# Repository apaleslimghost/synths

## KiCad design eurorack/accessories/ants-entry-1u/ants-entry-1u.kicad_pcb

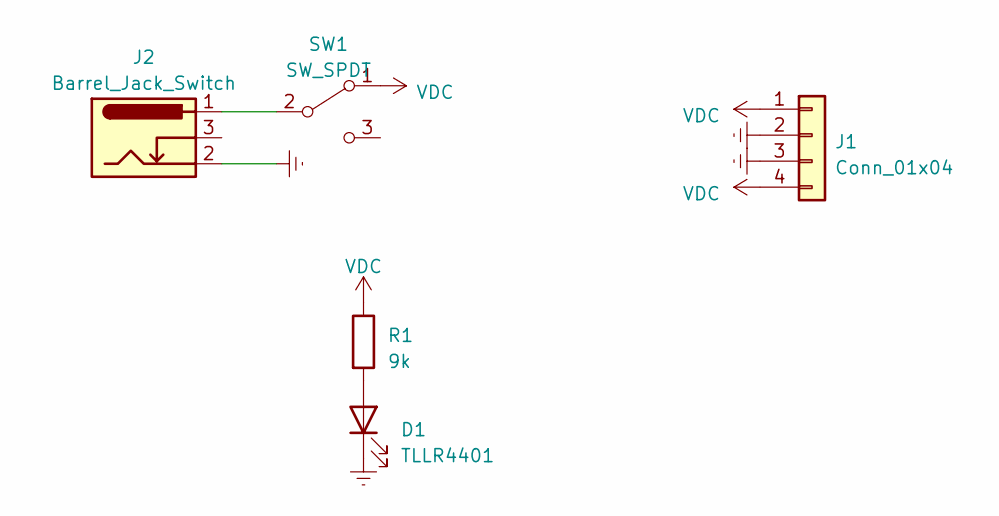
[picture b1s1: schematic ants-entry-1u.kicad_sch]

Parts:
D1: TLLR4401; LED_D3.0mm
J1: Conn_01x04; Molex_KK-254_AE-6410-04A_1x04_P2.54mm_Horizontal
J2: Barrel_Jack_Switch; CUI_PJ-064B
R1: 9k; R_Axial_DIN0207_L6.3mm_D2.5mm_P7.62mm_Horizontal
SW1: SW_SPDT; Sub Mini Toggle Switch SPDT

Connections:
Earth: D1.1 (K), J1.2, J1.3, J2.2
unnamed: D1.2 (A), R1.2
unnamed: J2.1, SW1.2 (B)
VDC: J1.1, J1.4, R1.1, SW1.1 (A)

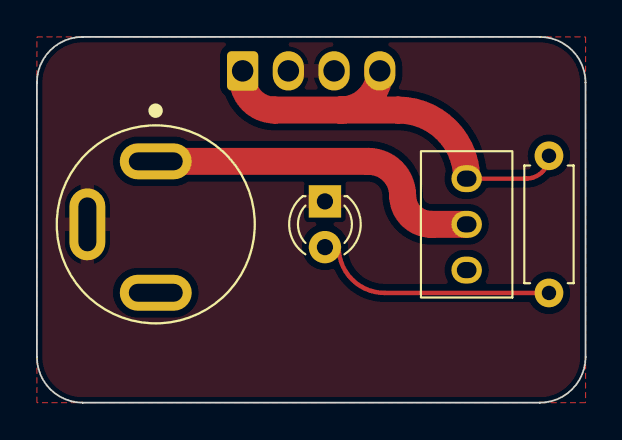
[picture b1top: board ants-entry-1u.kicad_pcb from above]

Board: 2 copper layers, 30.5 x 20.3 mm, 5 parts (1 on the bottom side), 4 nets.

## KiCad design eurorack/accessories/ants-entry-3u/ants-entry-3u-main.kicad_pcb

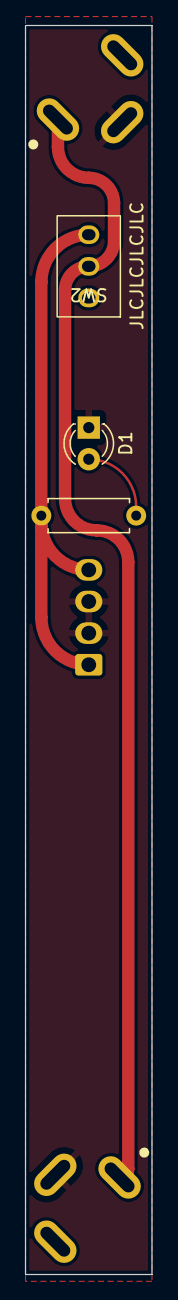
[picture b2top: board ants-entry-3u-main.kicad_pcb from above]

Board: 2 copper layers, 10.2 x 100.3 mm, 6 parts (1 on the bottom side), 4 nets.

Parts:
D1: TLLR4401; LED_D3.0mm
J1: Conn_01x04; Molex_KK-254_AE-6410-04A_1x04_P2.54mm_Vertical
J2, J3: Barrel_Jack_Switch; CUI_PJ-064B
R1: 9k; R_Axial_DIN0207_L6.3mm_D2.5mm_P7.62mm_Horizontal
SW2: SW_SPDT; Sub Mini Toggle Switch SPDT

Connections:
Earth: D1.1 (K), J1.2, J1.3, J2.2, J3.2
unnamed: D1.2 (A), R1.2
unnamed: J2.1, J3.1, SW2.2 (B)
VDC: J1.1, J1.4, R1.1, SW2.1 (A)

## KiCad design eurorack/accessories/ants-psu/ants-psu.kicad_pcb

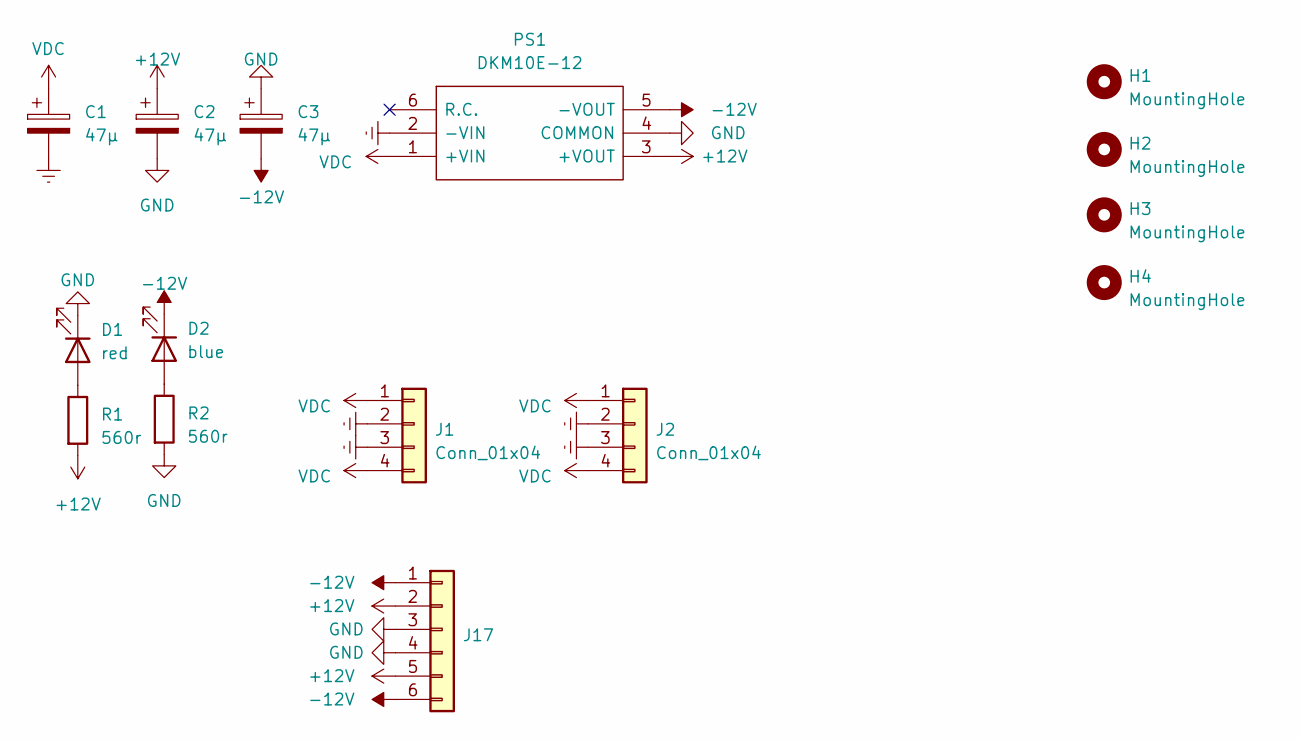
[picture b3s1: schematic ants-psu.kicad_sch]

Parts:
C1, C2, C3: 47μ; CP_Elec_5x4.5
D1: red; LED_0805_2012Metric_Pad1.15x1.40mm_HandSolder
D2: blue; LED_0805_2012Metric_Pad1.15x1.40mm_HandSolder
H1, H2, H3, H4: MountingHole; MountingHole_3.2mm_M3
J1, J2: Conn_01x04; Molex_KK-254_AE-6410-04A_1x04_P2.54mm_Horizontal
J17: Conn_01x06; Molex_KK-254_AE-6410-06A_1x06_P2.54mm_Horizontal
PS1: DKM10E-12; DKM10E12; Manufacturer_Part_Number DKM10E-12; Mouser Part Number 709-DKM10E-12
R1, R2: 560r; R_0805_2012Metric_Pad1.20x1.40mm_HandSolder

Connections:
+12V: C2.1, PS1.3 (+VOUT), R1.2; also elsewhere on the board
-12V: C3.2, D2.1 (K), PS1.5 (-VOUT); also elsewhere on the board
Earth: C1.2, J1.2, J1.3, J2.2, J2.3, PS1.2 (-VIN)
GND: C2.2, C3.1, D1.1 (K), PS1.4 (COMMON), R2.2; also elsewhere on the board
unnamed: D1.2 (A), R1.1
unnamed: D2.2 (A), R2.1
VDC: C1.1, J1.1, J1.4, J2.1, J2.4, PS1.1 (+VIN)

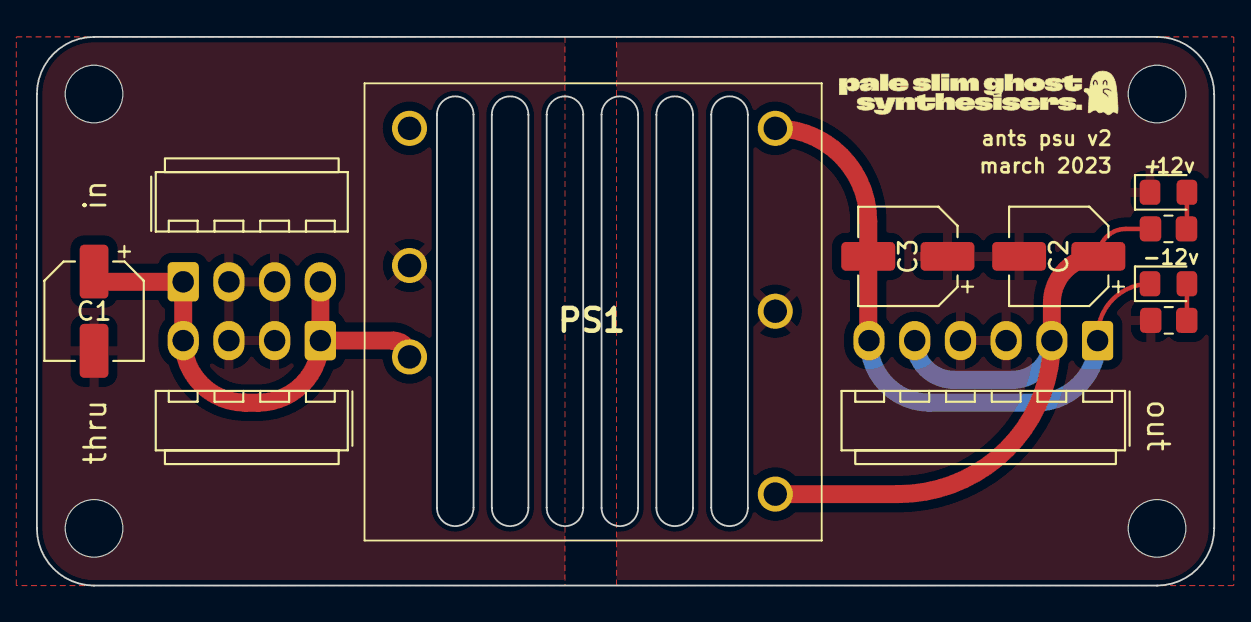
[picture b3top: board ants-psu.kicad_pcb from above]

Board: 2 copper layers, 65.4 x 30.5 mm, 15 parts (0 on the bottom side), 7 nets.

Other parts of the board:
J3: Conn_01x06; Molex_KK-254_AE-6410-06A_1x06_P2.54mm_Horizontal

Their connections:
+12V: J3.2, J3.5; also elsewhere on the board
-12V: J3.1, J3.6; also elsewhere on the board
GND: J3.3, J3.4; also elsewhere on the board

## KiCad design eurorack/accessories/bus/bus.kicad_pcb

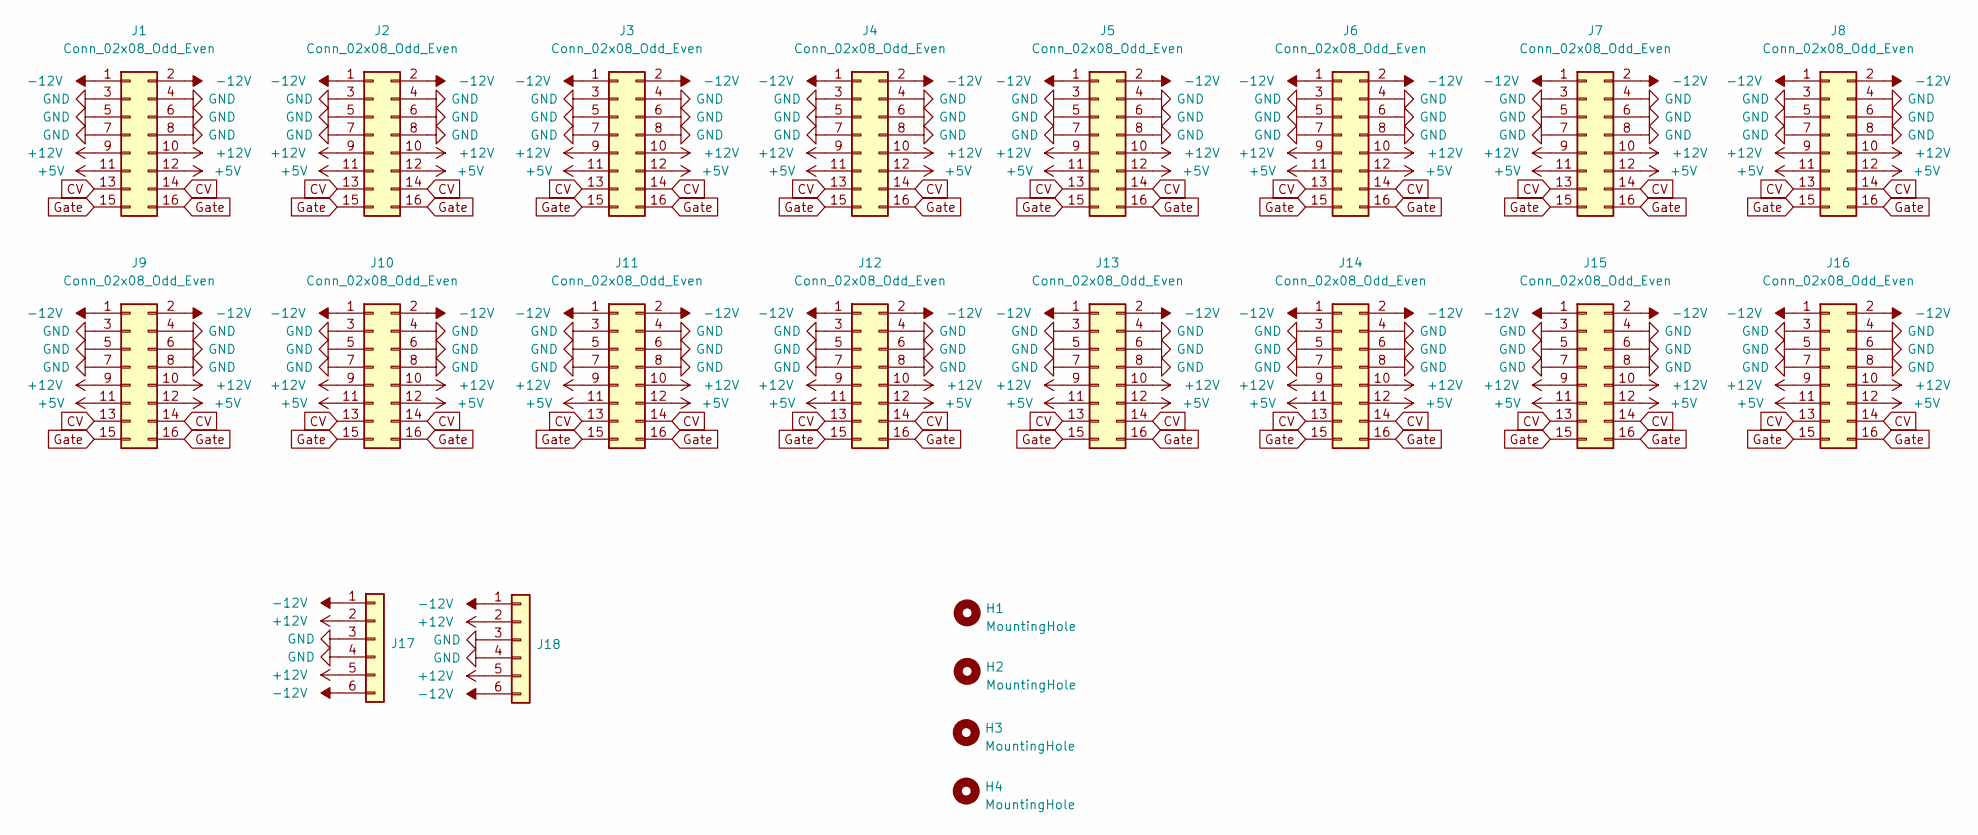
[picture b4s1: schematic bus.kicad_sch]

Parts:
H1, H2, H3, H4: MountingHole; MountingHole_3.2mm_M3
J1, J2, J3, J4, J5, J6, J7, J8, J9, J10, J11, J12, J13, J14, J15, J16: Conn_02x08_Odd_Even; PinHeader_2x08_P2.54mm_Edge
J17, J18: Conn_01x06; Molex_KK-254_AE-6410-06A_1x06_P2.54mm_Horizontal

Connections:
+5V: J1.11, J1.12, J2.11, J2.12, J3.11, J3.12, J4.11, J4.12, J5.11, J5.12, J6.11, J6.12, J7.11, J7.12, J8.11, J8.12, J9.11, J9.12, J10.11, J10.12, J11.11, J11.12, J12.11, J12.12, J13.11, J13.12, J14.11, J14.12, J15.11, J15.12, J16.11, J16.12
+12V: J1.9, J1.10, J2.9, J2.10, J3.9, J3.10, J4.9, J4.10, J5.9, J5.10, J6.9, J6.10, J7.9, J7.10, J8.9, J8.10, J9.9, J9.10, J10.9, J10.10, J11.9, J11.10, J12.9, J12.10, J13.9, J13.10, J14.9, J14.10, J15.9, J15.10, J16.9, J16.10, J17.2, J17.5, J18.2, J18.5
-12V: J1.1, J1.2, J2.1, J2.2, J3.1, J3.2, J4.1, J4.2, J5.1, J5.2, J6.1, J6.2, J7.1, J7.2, J8.1, J8.2, J9.1, J9.2, J10.1, J10.2, J11.1, J11.2, J12.1, J12.2, J13.1, J13.2, J14.1, J14.2, J15.1, J15.2, J16.1, J16.2, J17.1, J17.6, J18.1, J18.6
CV: J1.13, J1.14, J2.13, J2.14, J3.13, J3.14, J4.13, J4.14, J5.13, J5.14, J6.13, J6.14, J7.13, J7.14, J8.13, J8.14, J9.13, J9.14, J10.13, J10.14, J11.13, J11.14, J12.13, J12.14, J13.13, J13.14, J14.13, J14.14, J15.13, J15.14, J16.13, J16.14
GND: J1.3, J1.4, J1.5, J1.6, J1.7, J1.8, J2.3, J2.4, J2.5, J2.6, J2.7, J2.8, J3.3, J3.4, J3.5, J3.6, J3.7, J3.8, J4.3, J4.4, J4.5, J4.6, J4.7, J4.8, J5.3, J5.4, J5.5, J5.6, J5.7, J5.8, J6.3, J6.4, J6.5, J6.6, J6.7, J6.8, J7.3, J7.4, J7.5, J7.6, J7.7, J7.8, J8.3, J8.4, J8.5, J8.6, J8.7, J8.8, J9.3, J9.4, J9.5, J9.6, J9.7, J9.8, J10.3, J10.4, J10.5, J10.6, J10.7, J10.8, J11.3, J11.4, J11.5, J11.6, J11.7, J11.8, J12.3, J12.4, J12.5, J12.6, J12.7, J12.8, J13.3, J13.4, J13.5, J13.6, J13.7, J13.8, J14.3, J14.4, J14.5, J14.6, J14.7, J14.8, J15.3, J15.4, J15.5, J15.6, J15.7, J15.8, J16.3, J16.4, J16.5, J16.6, J16.7, J16.8, J17.3, J17.4, J18.3, J18.4
Gate: J1.15, J1.16, J2.15, J2.16, J3.15, J3.16, J4.15, J4.16, J5.15, J5.16, J6.15, J6.16, J7.15, J7.16, J8.15, J8.16, J9.15, J9.16, J10.15, J10.16, J11.15, J11.16, J12.15, J12.16, J13.15, J13.16, J14.15, J14.16, J15.15, J15.16, J16.15, J16.16

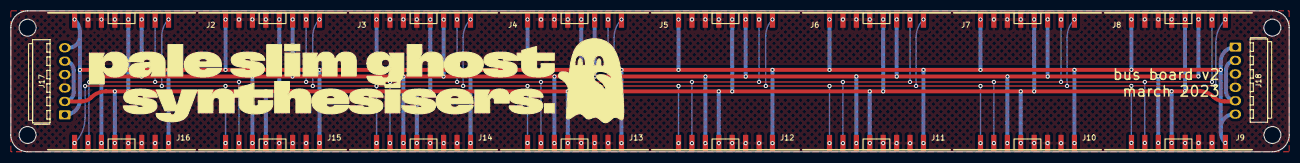
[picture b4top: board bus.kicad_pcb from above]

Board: 2 copper layers, 241.9 x 26.7 mm, 22 parts (0 on the bottom side), 6 nets.
